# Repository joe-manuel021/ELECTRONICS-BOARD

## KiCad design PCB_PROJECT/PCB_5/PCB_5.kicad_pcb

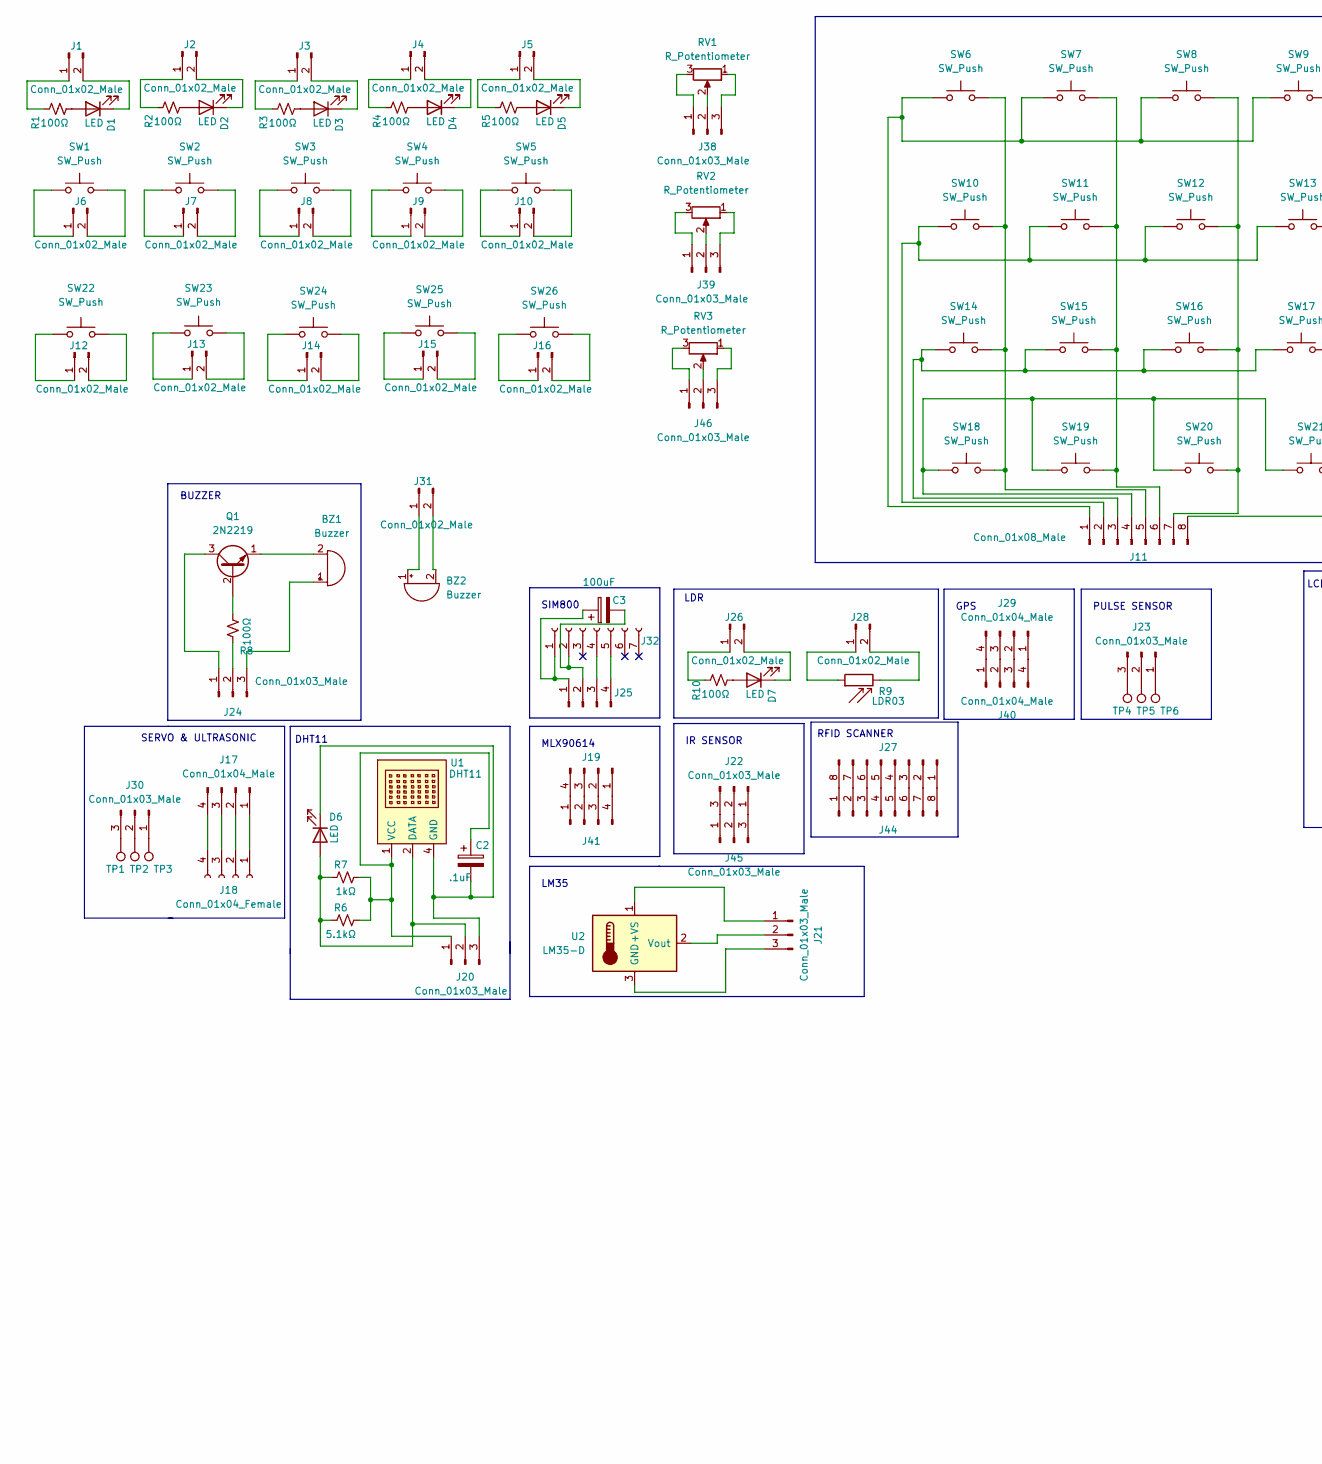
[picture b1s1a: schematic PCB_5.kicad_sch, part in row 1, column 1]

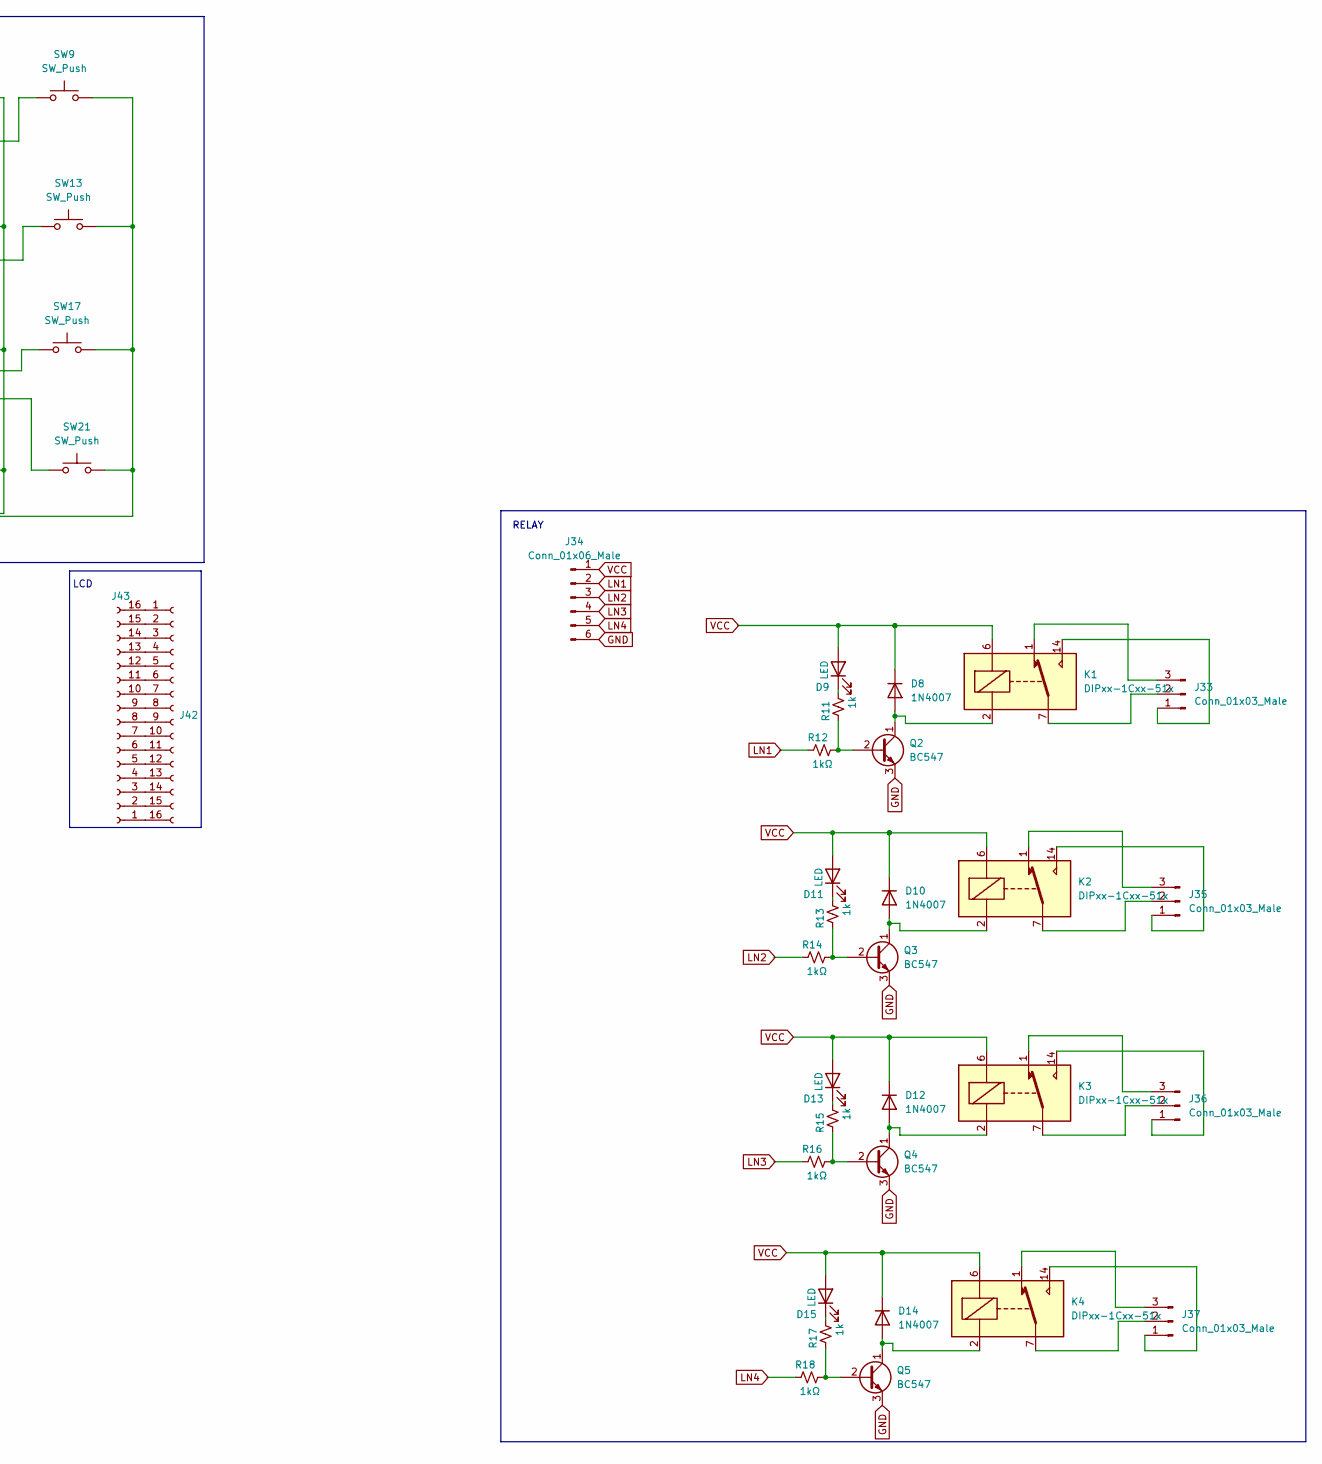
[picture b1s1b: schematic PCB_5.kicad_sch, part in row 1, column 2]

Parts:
BZ1, BZ2: Buzzer; MagneticBuzzer_ProSignal_ABI-010-RC
C2: .1uF; CP_Radial_D5.0mm_P2.50mm
C3: 100uF; CP_Radial_D8.0mm_P5.00mm
D1, D2, D3, D4, D5, D6, D7, D9, D11, D13, D15: LED; LED_D3.0mm
D8, D10, D12, D14: 1N4007; D_DO-41_SOD81_P10.16mm_Horizontal
J1, J2, J3, J4, J5, J6, J7, J8, J9, J10, J12, J13, J14, J15, J16, J26, J28, J31: Conn_01x02_Male; PinHeader_1x02_P2.54mm_Vertical
J11, J27, J44: Conn_01x08_Male; PinSocket_1x08_P2.54mm_Vertical
J17, J19, J25, J29, J40, J41: Conn_01x04_Male; PinHeader_1x04_P2.54mm_Vertical
J18: Conn_01x04_Female; PinSocket_1x04_P2.54mm_Vertical
J20, J21, J22, J23, J24, J30, J38, J39, J45, J46: Conn_01x03_Male; PinHeader_1x03_P2.54mm_Vertical
J32: Conn_01x07_Female; PinHeader_1x07_P2.54mm_Vertical
J33, J35, J36, J37: Conn_01x03_Male; TerminalBlock_bornier-3_P5.08mm
J34: Conn_01x06_Male; PinHeader_1x06_P2.54mm_Vertical
J42, J43: Conn_01x16_Female; PinSocket_1x16_P2.54mm_Vertical
K1, K2, K3, K4: DIPxx-1Cxx-51x; Relay_SPDT_Finder_36.11
Q1: 2N2219; TO-39-3
Q2, Q3, Q4, Q5: BC547; TO-92_Inline
R1, R2, R3, R4, R5, R8, R10: 100Ω; R_0805_2012Metric_Pad1.20x1.40mm_HandSolder
R6: 5.1kΩ; R_0805_2012Metric_Pad1.20x1.40mm_HandSolder
R7, R12, R14, R16, R18: 1kΩ; R_0805_2012Metric_Pad1.20x1.40mm_HandSolder
R9: LDR03; R_LDR_10x8.5mm_P7.6mm_Vertical
R11, R13, R15, R17: 1k; R_0805_2012Metric_Pad1.20x1.40mm_HandSolder
RV1, RV2, RV3: R_Potentiometer; Potentiometer_Piher_T-16L_Single_Vertical_Hole
SW1, SW2, SW3, SW4, SW5, SW6, SW7, SW8, SW9, SW10, SW11, SW12, SW13, SW14, SW15, SW16, SW17, SW18, SW19, SW20, SW21: SW_Push; SW_PUSH_6mm_H5mm
SW22, SW23, SW24, SW25, SW26: SW_Push; LATCH_BUTTON
TP1, TP2, TP3, TP4, TP5, TP6: TestPoint; TestPoint_Pad_4.0x4.0mm
U1: DHT11; PinSocket_1x04_P2.54mm_Vertical
U2: LM35-D; TO-92_Inline

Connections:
GND: J34.6, Q2.3 (E), Q3.3 (E), Q4.3 (E), Q5.3 (E)
LN1: J34.2, R12.2
LN2: J34.3, R14.2
LN3: J34.4, R16.2
LN4: J34.5, R18.2
unnamed: BZ1.1 (-), J24.3
unnamed: BZ1.2 (+), Q1.1 (E)
unnamed: BZ2.1 (-), J31.1
unnamed: BZ2.2 (+), J31.2
unnamed: C2.1, J20.1, R6.1, R7.1, U1.1 (VCC)
unnamed: C2.2, D6.1 (K), J20.3, U1.4 (GND)
unnamed: C3.1, J25.1, J32.1
unnamed: C3.2, J25.2, J32.2
unnamed: D1.1 (K), J1.2
unnamed: D1.2 (A), R1.1
unnamed: D2.1 (K), J2.2
unnamed: D2.2 (A), R2.1
unnamed: D3.1 (K), J3.2
unnamed: D3.2 (A), R3.1
unnamed: D4.1 (K), J4.2
unnamed: D4.2 (A), R4.1
unnamed: D5.1 (K), J5.2
unnamed: D5.2 (A), R5.1
unnamed: D6.2 (A), J20.2, R6.2, R7.2, U1.2 (DATA)
unnamed: D7.1 (K), J26.2
unnamed: D7.2 (A), R10.1
unnamed: D8.2 (A), K1.2, Q2.1 (C)
unnamed: D9.1 (K), R11.1
unnamed: D10.2 (A), K2.2, Q3.1 (C)
unnamed: D11.1 (K), R13.1
unnamed: D12.2 (A), K3.2, Q4.1 (C)
unnamed: D13.1 (K), R15.1
unnamed: D14.2 (A), K4.2, Q5.1 (C)
unnamed: D15.1 (K), R17.1
unnamed: J1.1, R1.2
unnamed: J2.1, R2.2
unnamed: J3.1, R3.2
unnamed: J4.1, R4.2
unnamed: J5.1, R5.2
unnamed: J6.1, SW1.2
unnamed: J6.2, SW1.1
unnamed: J7.1, SW2.2
unnamed: J7.2, SW2.1
unnamed: J8.1, SW3.2
unnamed: J8.2, SW3.1
unnamed: J9.1, SW4.2
unnamed: J9.2, SW4.1
unnamed: J10.1, SW5.2
unnamed: J10.2, SW5.1
unnamed: J11.1, SW6.2, SW7.2, SW8.2, SW9.2
unnamed: J11.2, SW10.2, SW11.2, SW12.2, SW13.2
unnamed: J11.3, SW14.2, SW15.2, SW16.2, SW17.2
unnamed: J11.4, SW18.2, SW19.2, SW20.2, SW21.2
unnamed: J11.5, SW6.1, SW10.1, SW14.1, SW18.1
unnamed: J11.6, SW7.1, SW11.1, SW15.1, SW19.1
unnamed: J11.7, SW8.1, SW12.1, SW16.1, SW20.1
unnamed: J11.8, SW9.1, SW13.1, SW17.1, SW21.1
unnamed: J12.1, SW22.2
unnamed: J12.2, SW22.1
unnamed: J13.1, SW23.2
unnamed: J13.2, SW23.1
unnamed: J14.1, SW24.2
unnamed: J14.2, SW24.1
unnamed: J15.1, SW25.2
unnamed: J15.2, SW25.1
unnamed: J16.1, SW26.2
unnamed: J16.2, SW26.1
unnamed: J17.1, J18.1
unnamed: J17.2, J18.2
unnamed: J17.3, J18.3
unnamed: J17.4, J18.4
unnamed: J19.1, J41.4
unnamed: J19.2, J41.3
unnamed: J19.3, J41.2
unnamed: J19.4, J41.1
unnamed: J21.1, U2.1 (+VS)
unnamed: J21.2, U2.2 (Vout)
unnamed: J22.1, J45.3
unnamed: J22.2, J45.2
unnamed: J22.3, J45.1
unnamed: J23.1, TP6.1
unnamed: J23.2, TP5.1
unnamed: J23.3, TP4.1
unnamed: J24.1, Q1.3 (C)
unnamed: J24.2, R8.2
unnamed: J25.3, J32.4
unnamed: J25.4, J32.5
unnamed: J26.1, R10.2
unnamed: J27.1, J44.8
unnamed: J27.2, J44.7
unnamed: J27.3, J44.6
unnamed: J27.4, J44.5
unnamed: J27.5, J44.4
unnamed: J27.6, J44.3
unnamed: J27.7, J44.2
unnamed: J27.8, J44.1
unnamed: J28.1, R9.1
unnamed: J28.2, R9.2
unnamed: J29.1, J40.4
unnamed: J29.2, J40.3
unnamed: J29.3, J40.2
unnamed: J29.4, J40.1
unnamed: J30.1, TP3.1
unnamed: J30.2, TP2.1
unnamed: J30.3, TP1.1
unnamed: J33.1, K1.14
unnamed: J33.2, K1.7, K1.8
unnamed: J33.3, K1.1
unnamed: J35.1, K2.14
unnamed: J35.2, K2.7, K2.8
unnamed: J35.3, K2.1
unnamed: J36.1, K3.14
unnamed: J36.2, K3.7, K3.8
unnamed: J36.3, K3.1
unnamed: J37.1, K4.14
unnamed: J37.2, K4.7, K4.8
unnamed: J37.3, K4.1
unnamed: J38.1, RV1.3
unnamed: J38.2, RV1.2
unnamed: J38.3, RV1.1
unnamed: J39.1, RV2.3
unnamed: J39.2, RV2.2
unnamed: J39.3, RV2.1
unnamed: J42.1, J43.16
unnamed: J42.2, J43.15
unnamed: J42.3, J43.14
unnamed: J42.4, J43.13
unnamed: J42.5, J43.12
unnamed: J42.6, J43.11
unnamed: J42.7, J43.10
unnamed: J42.8, J43.9
unnamed: J42.9, J43.8
unnamed: J42.10, J43.7
unnamed: J42.11, J43.6
unnamed: J42.12, J43.5
unnamed: J42.13, J43.4
unnamed: J42.14, J43.3
unnamed: J42.15, J43.2
unnamed: J42.16, J43.1
unnamed: Q1.2 (B), R8.1
unnamed: Q2.2 (B), R11.2, R12.1
unnamed: Q3.2 (B), R13.2, R14.1
unnamed: Q4.2 (B), R15.2, R16.1
unnamed: Q5.2 (B), R17.2, R18.1
unnamed: J46.3, RV3.1
unnamed: J46.2, RV3.2
unnamed: J46.1, RV3.3
unnamed: J21.3, U2.3 (GND)
VCC: D8.1 (K), D9.2 (A), D10.1 (K), D11.2 (A), D12.1 (K), D13.2 (A), D14.1 (K), D15.2 (A), J34.1, K1.6, K2.6, K3.6, K4.6

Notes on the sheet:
LM35
SIM800
PULSE SENSOR
DHT11
BUZZER
LDR
GPS
LCD
IR SENSOR
RELAY
MLX90614
RFID SCANNER
SERVO & ULTRASONIC

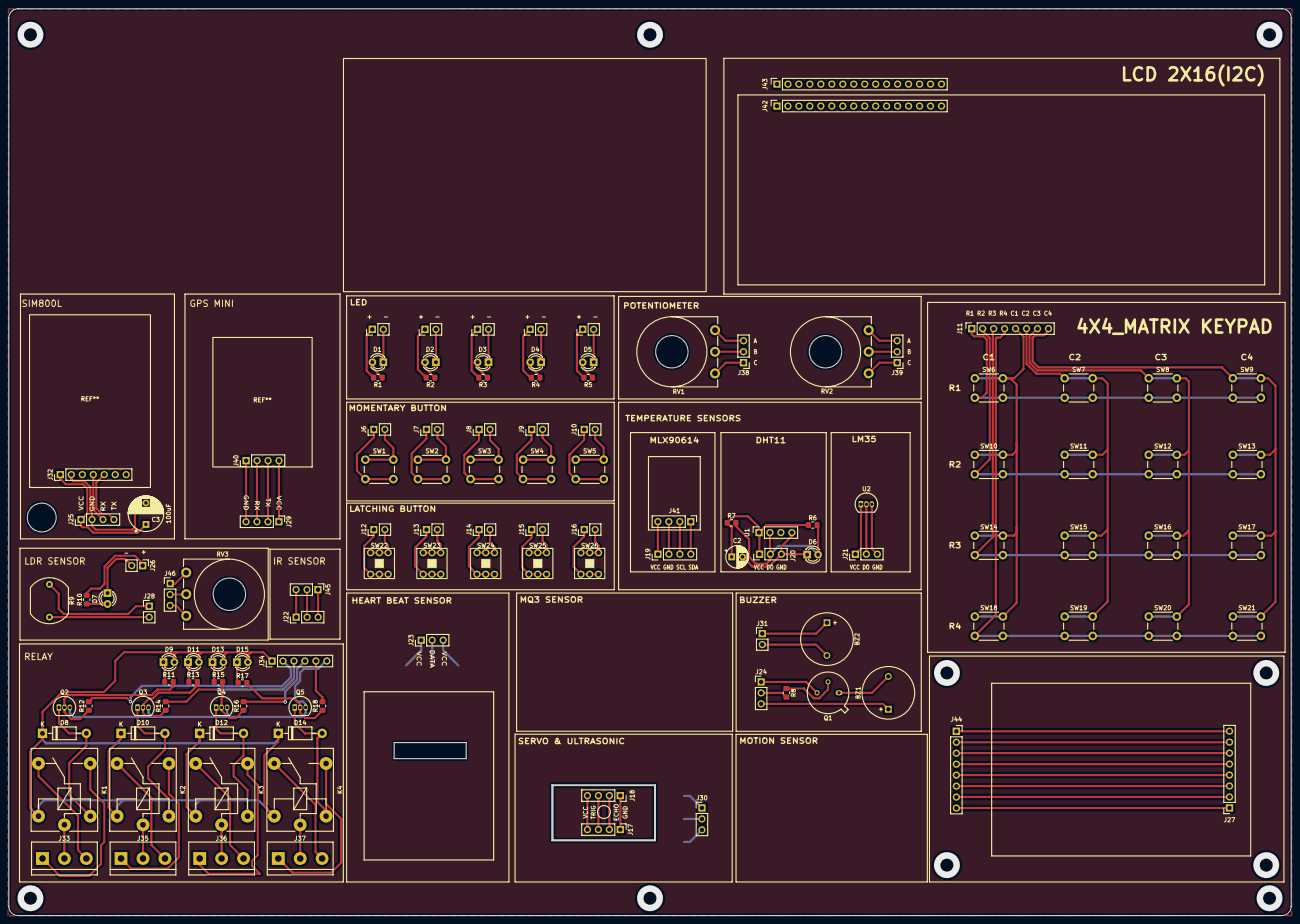
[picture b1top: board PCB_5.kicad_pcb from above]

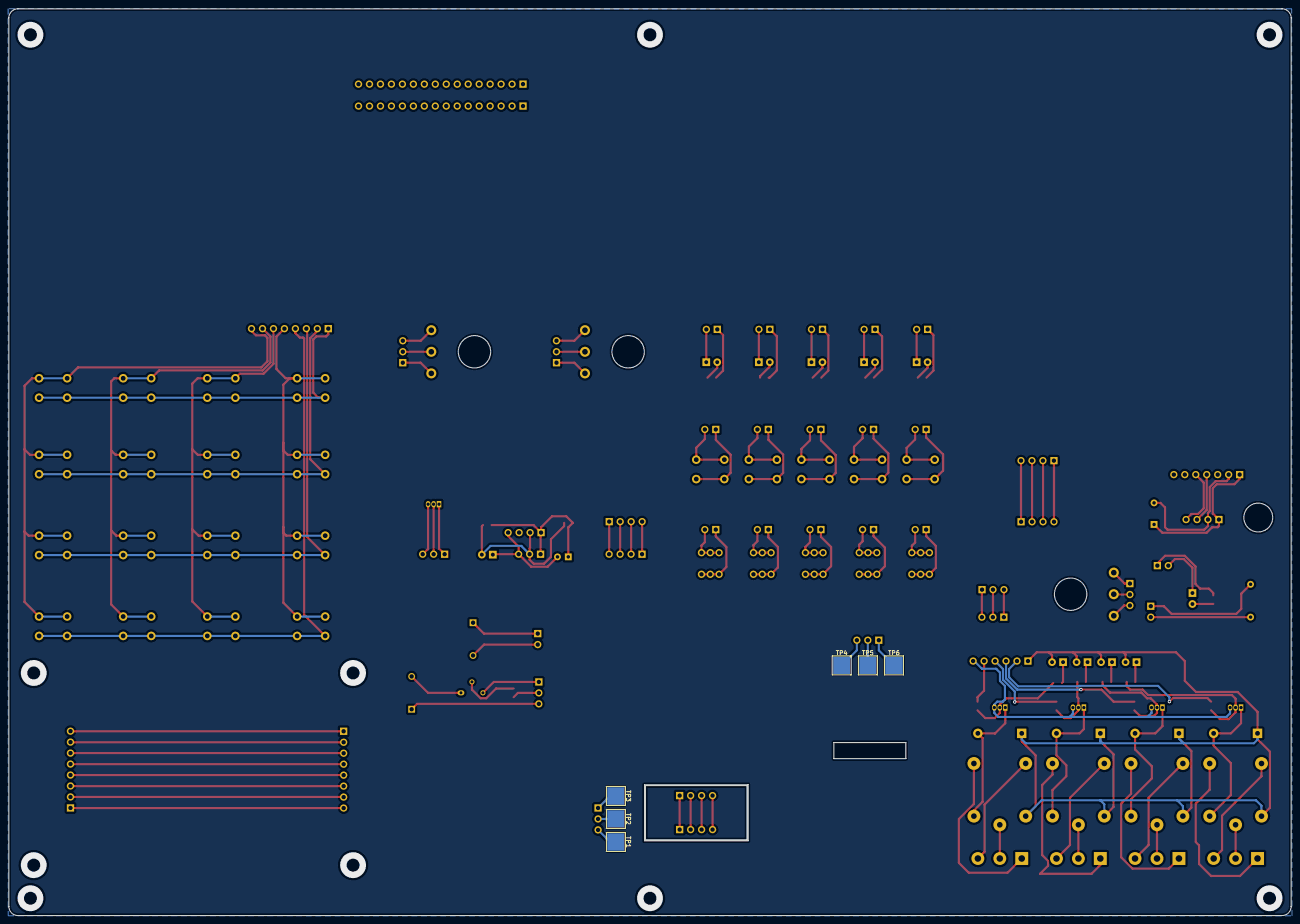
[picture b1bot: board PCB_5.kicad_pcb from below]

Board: 2 copper layers, 297.0 x 210.0 mm, 130 parts (6 on the bottom side), 149 nets.

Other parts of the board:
 : breadboard_small

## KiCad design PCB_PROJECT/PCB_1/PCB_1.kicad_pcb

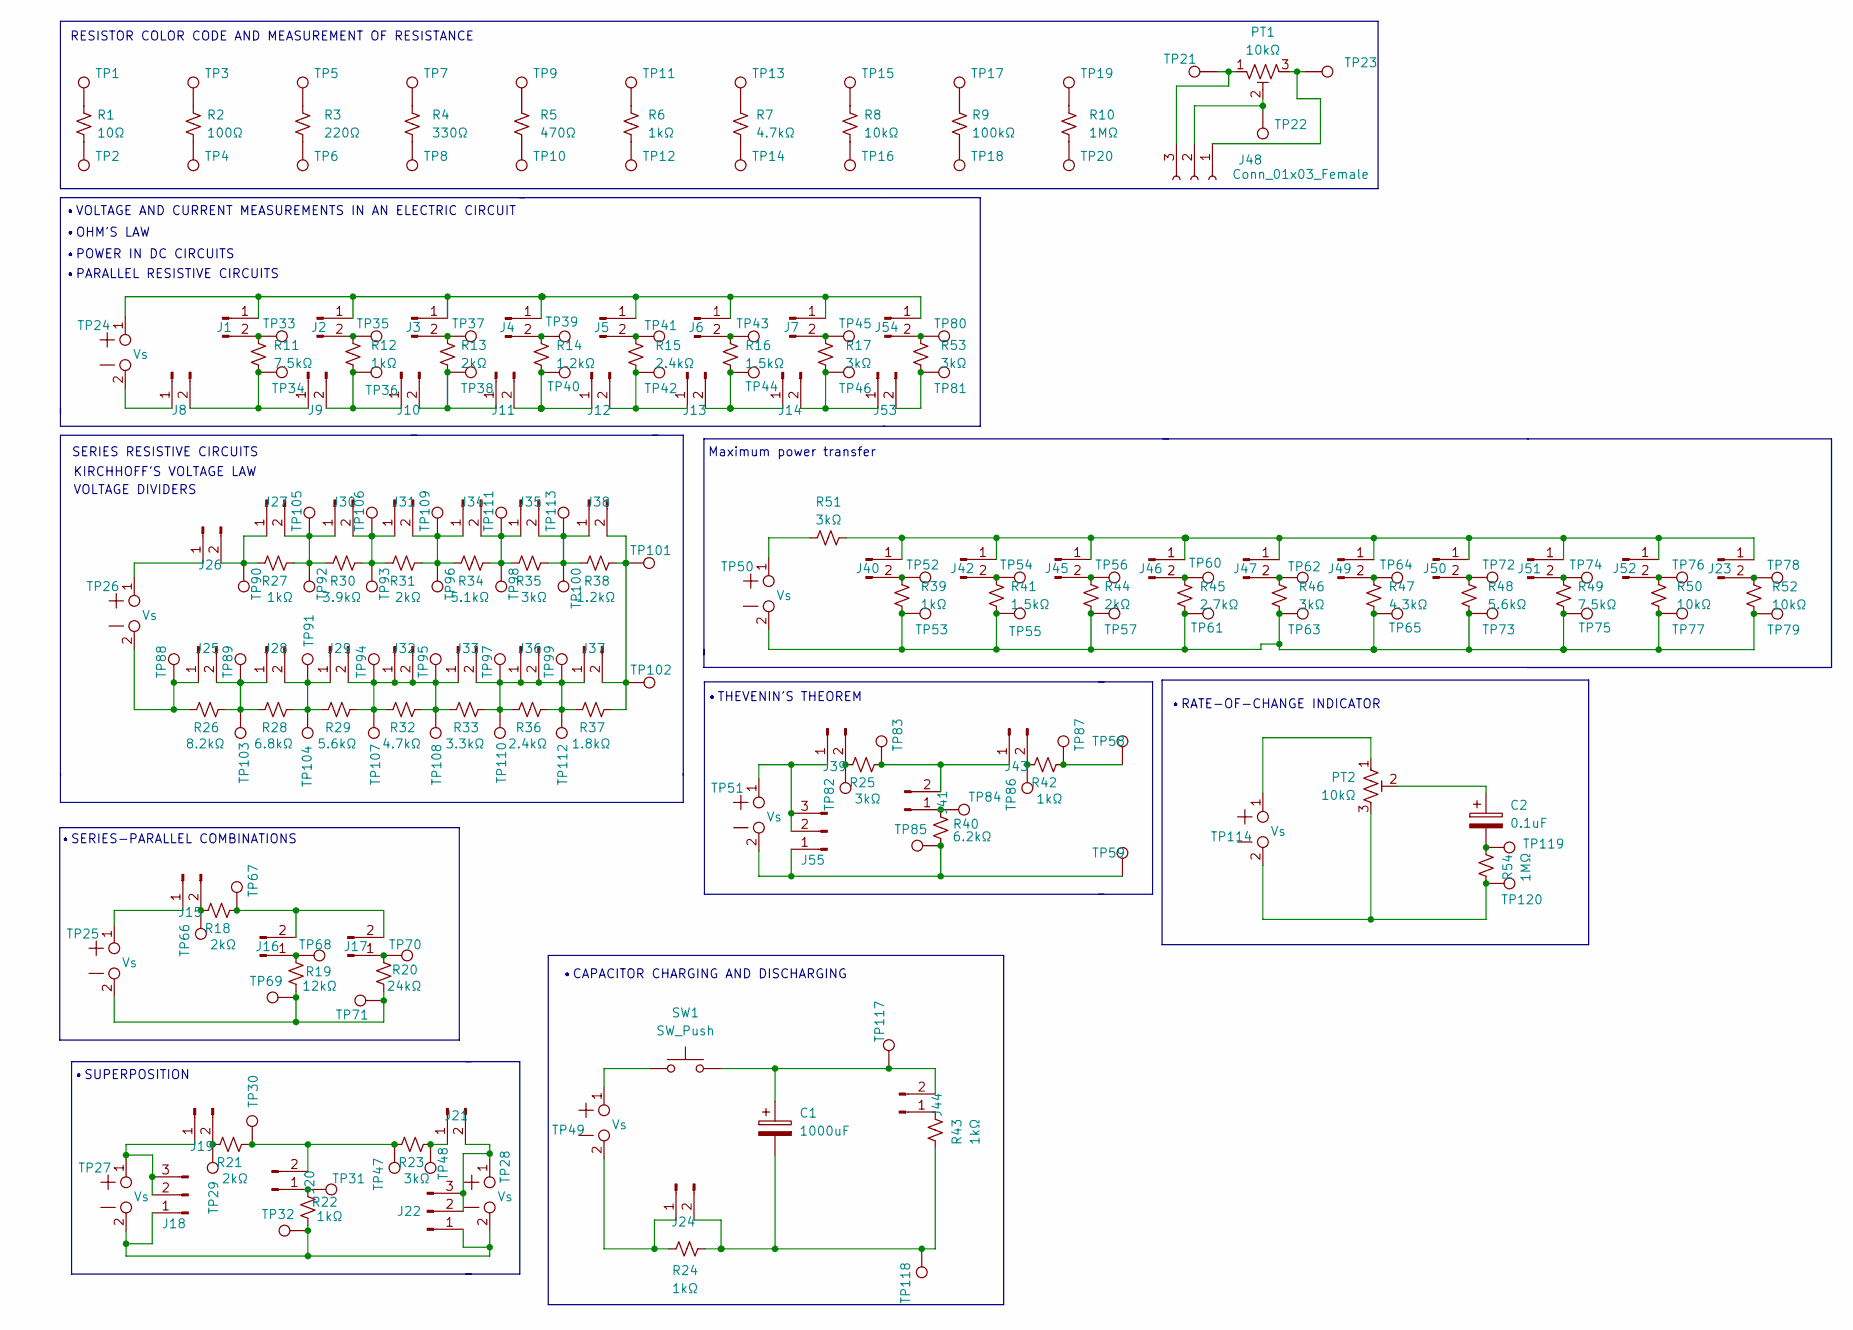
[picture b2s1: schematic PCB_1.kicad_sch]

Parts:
C1: 1000uF; CP_Radial_D13.0mm_P7.50mm
C2: 0.1uF; C_Disc_D12.5mm_W5.0mm_P10.00mm
J1, J2, J3, J4, J5, J6, J7, J23, J39, J40, J41, J42, J43, J44, J45, J46, J47, J49, J50, J51, J52, J54: Jumper_White
J8, J9, J10, J11, J12, J13, J14, J15, J16, J17, J19, J20, J21, J26, J53: PinHeader_1x02_P2.54mm_Vertical_Yellow
J18, J22, J55: Conn_01x03_Male; PinSocket_1x03_P2.54mm_Vertical
J24, J25, J27, J28, J29, J30, J31, J32, J33, J34, J35, J36, J37, J38: PinHeader_1x02_P2.54mm_Vertical_Blue
J48: Conn_01x03_Female; PinHeader_1x03_P2.54mm_Vertical
PT1, PT2: 10kΩ; Potentiometer_Alps_RK163_Single_Horizontal
R1: 10Ω; R_Axial_DIN0411_L9.9mm_D3.6mm_P15.24mm_Horizontal
R2: 100Ω; R_Axial_DIN0411_L9.9mm_D3.6mm_P15.24mm_Horizontal
R3: 220Ω; R_Axial_DIN0411_L9.9mm_D3.6mm_P15.24mm_Horizontal
R4: 330Ω; R_Axial_DIN0411_L9.9mm_D3.6mm_P15.24mm_Horizontal
R5: 470Ω; R_Axial_DIN0411_L9.9mm_D3.6mm_P15.24mm_Horizontal
R6, R12, R22, R24, R27, R39, R42, R43: 1kΩ; R_Axial_DIN0411_L9.9mm_D3.6mm_P15.24mm_Horizontal
R7, R32: 4.7kΩ; R_Axial_DIN0411_L9.9mm_D3.6mm_P15.24mm_Horizontal
R8, R50, R52: 10kΩ; R_Axial_DIN0411_L9.9mm_D3.6mm_P15.24mm_Horizontal
R9: 100kΩ; R_Axial_DIN0411_L9.9mm_D3.6mm_P15.24mm_Horizontal
R10, R54: 1MΩ; R_Axial_DIN0411_L9.9mm_D3.6mm_P15.24mm_Horizontal
R11, R49: 7.5kΩ; R_Axial_DIN0411_L9.9mm_D3.6mm_P15.24mm_Horizontal
R13, R18, R21, R31, R44: 2kΩ; R_Axial_DIN0411_L9.9mm_D3.6mm_P15.24mm_Horizontal
R14, R38: 1.2kΩ; R_Axial_DIN0411_L9.9mm_D3.6mm_P15.24mm_Horizontal
R15, R36: 2.4kΩ; R_Axial_DIN0411_L9.9mm_D3.6mm_P15.24mm_Horizontal
R16, R41: 1.5kΩ; R_Axial_DIN0411_L9.9mm_D3.6mm_P15.24mm_Horizontal
R17, R23, R25, R35, R46, R51, R53: 3kΩ; R_Axial_DIN0411_L9.9mm_D3.6mm_P15.24mm_Horizontal
R19: 12kΩ; R_Axial_DIN0411_L9.9mm_D3.6mm_P15.24mm_Horizontal
R20: 24kΩ; R_Axial_DIN0411_L9.9mm_D3.6mm_P15.24mm_Horizontal
R26: 8.2kΩ; R_Axial_DIN0411_L9.9mm_D3.6mm_P15.24mm_Horizontal
R28: 6.8kΩ; R_Axial_DIN0411_L9.9mm_D3.6mm_P15.24mm_Horizontal
R29, R48: 5.6kΩ; R_Axial_DIN0411_L9.9mm_D3.6mm_P15.24mm_Horizontal
R30: 3.9kΩ; R_Axial_DIN0411_L9.9mm_D3.6mm_P15.24mm_Horizontal
R33: 3.3kΩ; R_Axial_DIN0411_L9.9mm_D3.6mm_P15.24mm_Horizontal
R34: 5.1kΩ; R_Axial_DIN0411_L9.9mm_D3.6mm_P15.24mm_Horizontal
R37: 1.8kΩ; R_Axial_DIN0411_L9.9mm_D3.6mm_P15.24mm_Horizontal
R40: 6.2kΩ; R_Axial_DIN0411_L9.9mm_D3.6mm_P15.24mm_Horizontal
R45: 2.7kΩ; R_Axial_DIN0411_L9.9mm_D3.6mm_P15.24mm_Horizontal
R47: 4.3kΩ; R_Axial_DIN0411_L9.9mm_D3.6mm_P15.24mm_Horizontal
SW1: SW_Push; SW_DIP_SPSTx01_Slide_9.78x4.72mm_W7.62mm_P2.54mm
TP1, TP2, TP3, TP4, TP5, TP6, TP7, TP8, TP9, TP10, TP11, TP12, TP13, TP14, TP15, TP16, TP17, TP18, TP19, TP20, TP21, TP22, TP23, TP29, TP30, TP31, TP32, TP33, TP34, TP35, TP36, TP37, TP38, TP39, TP40, TP41, TP42, TP43, TP44, TP45, TP46, TP47, TP48, TP52, TP53, TP54, TP55, TP56, TP57, TP58, TP59, TP60, TP61, TP62, TP63, TP64, TP65, TP66, TP67, TP68, TP69, TP70, TP71, TP72, TP73, TP74, TP75, TP76, TP77, TP78, TP79, TP80, TP81, TP82, TP83, TP84, TP85, TP86, TP87, TP88, TP89, TP90, TP91, TP92, TP93, TP94, TP95, TP96, TP97, TP98, TP99, TP100, TP101, TP102, TP103, TP104, TP105, TP106, TP107, TP108, TP109, TP110, TP111, TP112, TP113, TP117, TP118, TP119, TP120: 2.5_TP_1.5
TP24, TP25, TP26, TP27, TP28, TP49, TP50, TP51, TP114: Vs; TestPoint_Pith10mm_Drill4mm

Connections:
unnamed: C1.1, J44.2, SW1.1, TP117.1
unnamed: C1.2, J24.2, R24.1, R43.2, TP118.1
unnamed: C2.1, PT2.2
unnamed: C2.2, R54.1, TP119.1
unnamed: J1.1, J2.1, J3.1, J4.1, J5.1, J6.1, J7.1, J54.1, TP24.1
unnamed: J1.2, R11.2, TP33.1
unnamed: J2.2, R12.2, TP35.1
unnamed: J3.2, R13.2, TP37.1
unnamed: J4.2, R14.2, TP39.1
unnamed: J5.2, R15.2, TP41.1
unnamed: J6.2, R16.2, TP43.1
unnamed: J7.2, R17.2, TP45.1
unnamed: J8.1, TP24.2
unnamed: J8.2, J9.1, R11.1, TP34.1
unnamed: J9.2, J10.1, R12.1, TP36.1
unnamed: J10.2, J11.1, R13.1, TP38.1
unnamed: J11.2, J12.1, R14.1, TP40.1
unnamed: J12.2, J13.1, R15.1, TP42.1
unnamed: J13.2, J14.1, R16.1, TP44.1
unnamed: J14.2, J53.1, R17.1, TP46.1
unnamed: J15.1, TP25.1
unnamed: J15.2, R18.2, TP66.1
unnamed: J16.1, R19.1, TP68.1
unnamed: J16.2, J17.2, R18.1, TP67.1
unnamed: J17.1, R20.1, TP70.1
unnamed: J18.1, J22.1, R22.2, TP27.2, TP28.2, TP32.1
unnamed: J18.2, J18.3, J19.1, TP27.1
unnamed: J19.2, R21.2, TP29.1
unnamed: J20.1, R22.1, TP31.1
unnamed: J20.2, R21.1, R23.2, TP30.1, TP47.1
unnamed: J21.1, R23.1, TP48.1
unnamed: J21.2, J22.2, J22.3, TP28.1
unnamed: J23.1, J40.1, J42.1, J45.1, J46.1, J47.1, J49.1, J50.1, J51.1, J52.1, R51.1
unnamed: J23.2, R52.2, TP78.1
unnamed: J24.1, R24.2, TP49.2
unnamed: J25.1, R26.2, TP26.2, TP88.1
unnamed: J25.2, J28.1, R26.1, R28.2, TP89.1, TP103.1
unnamed: J26.1, TP26.1
unnamed: J26.2, J27.1, R27.2, TP90.1
unnamed: J27.2, J30.1, R27.1, R30.2, TP92.1, TP105.1
unnamed: J28.2, J29.1, R28.1, R29.2, TP91.1, TP104.1
unnamed: J29.2, J32.1, R29.1, R32.2, TP94.1, TP107.1
unnamed: J30.2, J31.1, R30.1, R31.2, TP93.1, TP106.1
unnamed: J31.2, J34.1, R31.1, R34.2, TP96.1, TP109.1
unnamed: J32.2, J33.1, R32.1, R33.2, TP95.1, TP108.1
unnamed: J33.2, J36.1, R33.1, R36.2, TP97.1, TP110.1
unnamed: J34.2, J35.1, R34.1, R35.2, TP98.1, TP111.1
unnamed: J35.2, J38.1, R35.1, R38.2, TP100.1, TP113.1
unnamed: J36.2, J37.1, R36.1, R37.2, TP99.1, TP112.1
unnamed: J37.2, J38.2, R37.1, R38.1, TP101.1, TP102.1
unnamed: J39.1, J55.2, J55.3, TP51.1
unnamed: J39.2, R25.2, TP82.1
unnamed: J40.2, R39.2, TP52.1
unnamed: J41.1, R40.1, TP84.1
unnamed: J41.2, J43.1, R25.1, TP83.1
unnamed: J42.2, R41.2, TP54.1
unnamed: J43.2, R42.2, TP86.1
unnamed: J44.1, R43.1
unnamed: J45.2, R44.2, TP56.1
unnamed: J46.2, R45.2, TP60.1
unnamed: J47.2, R46.2, TP62.1
unnamed: J48.1, PT1.3, TP23.1
unnamed: J48.2, PT1.2, TP22.1
unnamed: J48.3, PT1.1, TP21.1
unnamed: J49.2, R47.2, TP64.1
unnamed: J50.2, R48.2, TP72.1
unnamed: J51.2, R49.2, TP74.1
unnamed: J52.2, R50.2, TP76.1
unnamed: J53.2, R53.1, TP81.1
unnamed: J54.2, R53.2, TP80.1
unnamed: J55.1, R40.2, TP51.2, TP59.1, TP85.1
unnamed: PT2.1, TP114.1
unnamed: PT2.3, R54.2, TP114.2, TP120.1
unnamed: R1.1, TP2.1
unnamed: R1.2, TP1.1
unnamed: R2.1, TP4.1
unnamed: R2.2, TP3.1
unnamed: R3.1, TP6.1
unnamed: R3.2, TP5.1
unnamed: R4.1, TP8.1
unnamed: R4.2, TP7.1
unnamed: R5.1, TP10.1
unnamed: R5.2, TP9.1
unnamed: R6.1, TP12.1
unnamed: R6.2, TP11.1
unnamed: R7.1, TP14.1
unnamed: R7.2, TP13.1
unnamed: R8.1, TP16.1
unnamed: R8.2, TP15.1
unnamed: R9.1, TP18.1
unnamed: R9.2, TP17.1
unnamed: R10.1, TP20.1
unnamed: R10.2, TP19.1
unnamed: R19.2, R20.2, TP25.2, TP69.1, TP71.1
unnamed: R39.1, R41.1, R44.1, R45.1, R46.1, R47.1, R48.1, R49.1, R50.1, R52.1, TP50.2, TP53.1, TP55.1, TP57.1, TP61.1, TP63.1, TP65.1, TP73.1, TP75.1, TP77.1, TP79.1
unnamed: R42.1, TP58.1, TP87.1
unnamed: R51.2, TP50.1
unnamed: SW1.2, TP49.1

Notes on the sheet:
•RATE-OF-CHANGE INDICATOR
•THEVENIN'S THEOREM
•OHM'S LAW
•PARALLEL RESISTIVE CIRCUITS
VOLTAGE DIVIDERS
•SERIES-PARALLEL COMBINATIONS
•VOLTAGE AND CURRENT MEASUREMENTS IN AN ELECTRIC CIRCUIT
SERIES RESISTIVE CIRCUITS
•POWER IN DC CIRCUITS
RESISTOR COLOR CODE AND MEASUREMENT OF RESISTANCE
KIRCHHOFF’S VOLTAGE LAW
•SUPERPOSITION
Maximum power transfer
•CAPACITOR CHARGING AND DISCHARGING

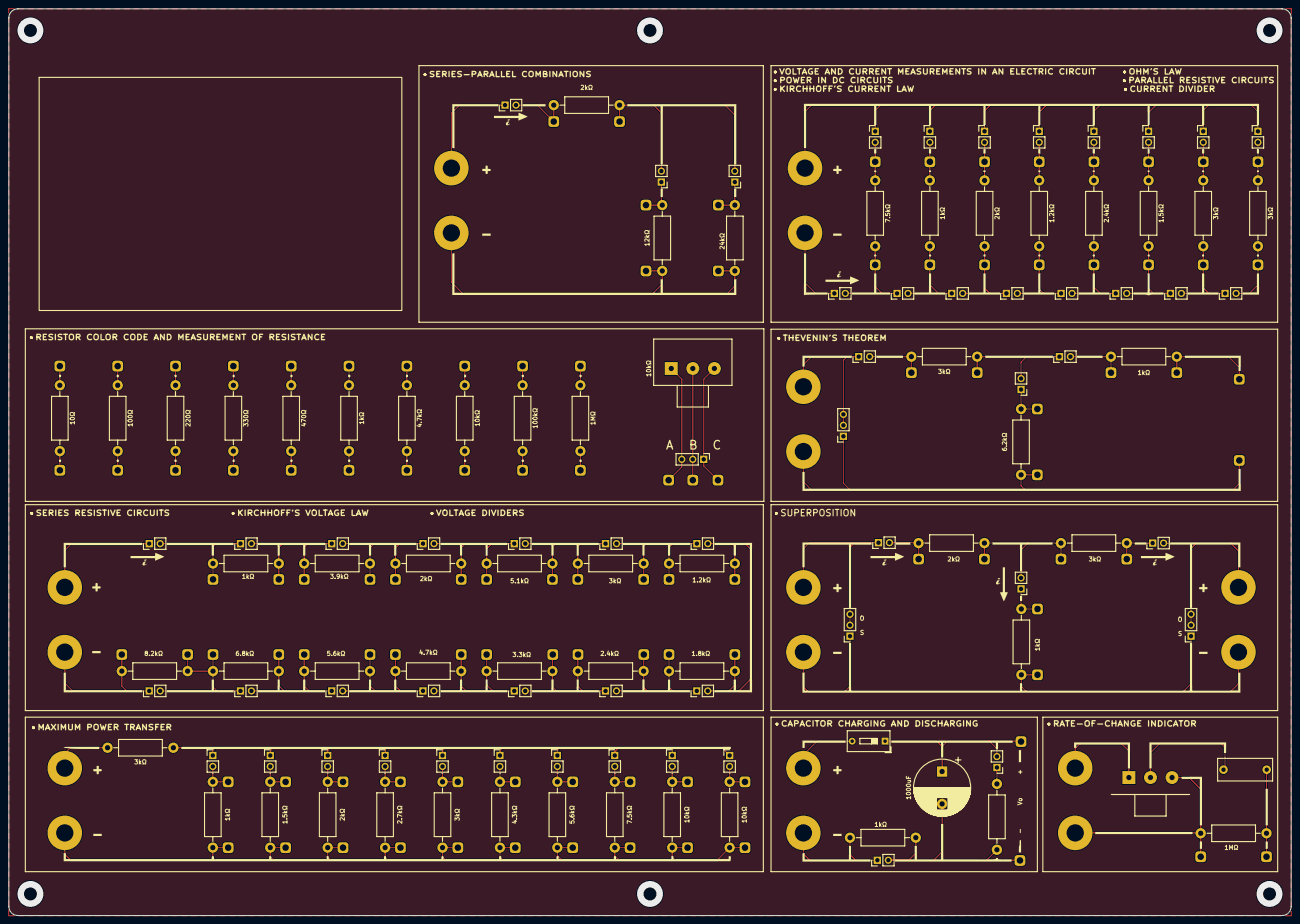
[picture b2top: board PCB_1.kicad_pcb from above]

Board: 2 copper layers, 297.0 x 210.0 mm, 233 parts (0 on the bottom side), 98 nets.

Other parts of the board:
 : LOGO; PB1_ALL
